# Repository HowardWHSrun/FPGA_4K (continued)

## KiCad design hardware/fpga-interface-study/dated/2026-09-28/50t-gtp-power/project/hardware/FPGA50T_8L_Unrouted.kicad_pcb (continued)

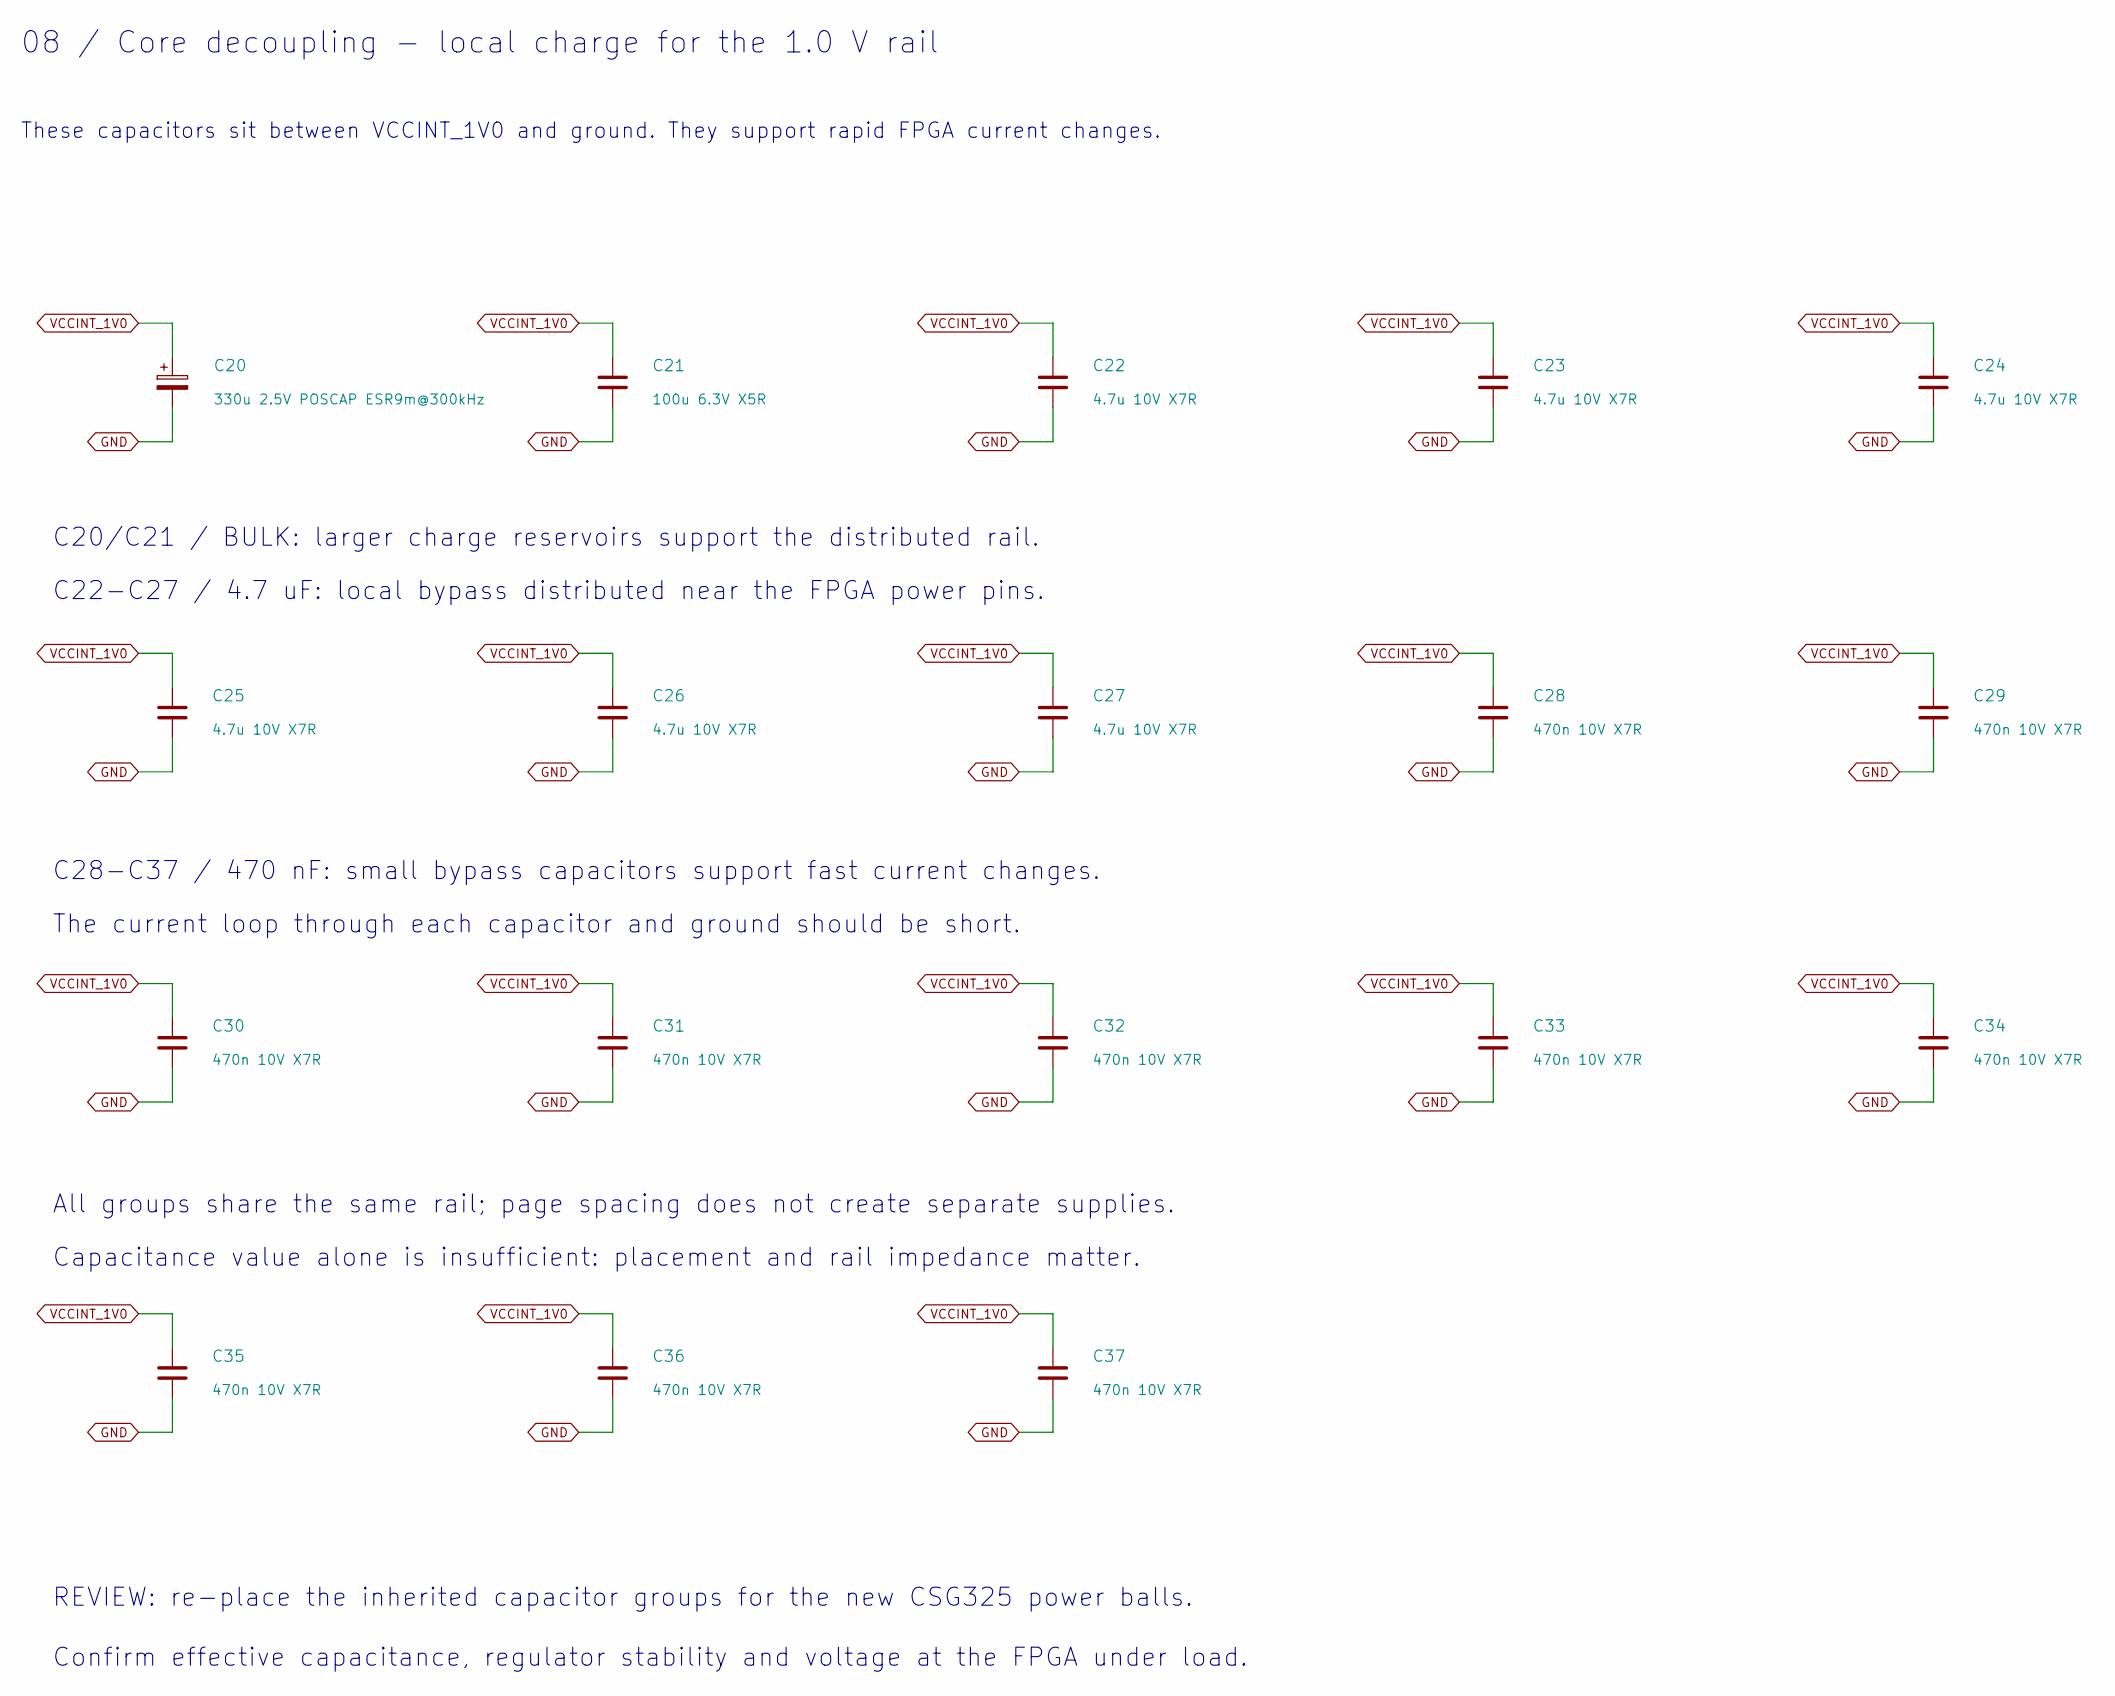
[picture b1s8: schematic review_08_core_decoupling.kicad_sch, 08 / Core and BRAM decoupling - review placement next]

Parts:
C20: 330u 2.5V POSCAP ESR9m@300kHz; Panasonic_POSCAP_B2_Recommended; MPN ETPE330M9GB
C21: 100u 6.3V X5R; Capacitor_SMD__C_1210_3225Metric; MPN GRM32ER60J107ME20L
C22, C23, C24, C25, C26, C27: 4.7u 10V X7R; Capacitor_SMD__C_0805_2012Metric; MPN GRM21BR71A475KA73L
C28, C29, C30, C31, C32, C33, C34, C35, C36, C37: 470n 10V X7R; Murata_GRT15_0402_Recommended; MPN GRT155R71A474KE01D

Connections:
GND: C20.2, C21.2, C22.2, C23.2, C24.2, C25.2, C26.2, C27.2, C28.2, C29.2, C30.2, C31.2, C32.2, C33.2, C34.2, C35.2, C36.2, C37.2; also elsewhere on the board
VCCINT_1V0: C20.1, C21.1, C22.1, C23.1, C24.1, C25.1, C26.1, C27.1, C28.1, C29.1, C30.1, C31.1, C32.1, C33.1, C34.1, C35.1, C36.1, C37.1; also elsewhere on the board

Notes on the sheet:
08 / Core decoupling - local charge for the 1.0 V rail
These capacitors sit between VCCINT_1V0 and ground. They support rapid FPGA current changes.
C20/C21 / BULK: larger charge reservoirs support the distributed rail.
C22-C27 / 4.7 uF: local bypass distributed near the FPGA power pins.
C28-C37 / 470 nF: small bypass capacitors support fast current changes.
The current loop through each capacitor and ground should be short.
All groups share the same rail; page spacing does not create separate supplies.
Capacitance value alone is insufficient: placement and rail impedance matter.
REVIEW: re-place the inherited capacitor groups for the new CSG325 power balls.
Confirm effective capacitance, regulator stability and voltage at the FPGA under load.

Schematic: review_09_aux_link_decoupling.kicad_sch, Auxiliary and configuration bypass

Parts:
C40, C50, C92: 47u 6.3V X7R; Capacitor_SMD__C_1210_3225Metric; MPN GRM32ER70J476ME20L
C41, C42, C51, C52: 4.7u 10V X7R; Capacitor_SMD__C_0805_2012Metric; MPN GRM21BR71A475KA73L
C43, C44, C45, C46, C53, C54, C55, C56: 470n 10V X7R; Murata_GRT15_0402_Recommended; MPN GRT155R71A474KE01D
C90: 100n 16V X7R; Murata_GRT15_0402_Recommended; MPN GRT155R71C104KE01D
C91: 1u 10V X7R; Capacitor_SMD__C_0603_1608Metric; MPN GRM188R71A105KA61D

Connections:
GND: C40.2, C41.2, C42.2, C43.2, C44.2, C45.2, C46.2, C50.2, C51.2, C52.2, C53.2, C54.2, C55.2, C56.2, C90.2, C91.2, C92.2; also elsewhere on the board
VCCAUX_1V8: C40.1, C41.1, C42.1, C43.1, C44.1, C45.1, C46.1, C50.1, C51.1, C52.1, C53.1, C54.1, C55.1, C56.1, C90.1, C91.1, C92.1; also elsewhere on the board

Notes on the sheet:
09 / Auxiliary and configuration bypass
Capacitor groups show placement intent; equal net names are one electrical supply across the board.
1.8 V / AUXILIARY GROUP
CONFIGURATION / SHARED 1.8 V GROUP
C40-C46 + C90/C91 / 1.8 V
These all connect to VCCAUX_1V8.
Large capacitors hold local charge;
smaller values support fast changes.
Review placement near auxiliary/XADC
power pins rather than treating this
as an already isolated analog supply.
C50-C56 + C92 / ALSO 1.8 V
These use the same auxiliary net.
The configuration bank now uses 1.8 V.
The three user I/O banks use 1.5 V.
Redistribute inherited bank capacitors
after reviewing the CSG325 pin map.
NEXT: assign each bypass group to its actual power balls and check the complete power-distribution network.
UNUSED 2.5 V GROUP REMOVED
C57-C63 are no longer fitted.
U4 now feeds GTP1.2 V on sheet13.
New GTP bypass capacitors have
separate analog supply nets.

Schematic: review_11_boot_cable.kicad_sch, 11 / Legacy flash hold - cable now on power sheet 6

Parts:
C100: 100n; Capacitor_SMD__C_0402_1005Metric; MPN GRM155R71C104KA88D
C101: 1u 16V X5R; Capacitor_SMD__C_0402_1005Metric; MPN GRM155R61C105KA12D
R100: 2.4k; Resistor_SMD__R_0402_1005Metric; MPN CRCW04022K40FKED
R101, R102: 4.7k; Resistor_SMD__R_0402_1005Metric; MPN CRCW04024K70FKED
R103, R105: 33; Resistor_SMD__R_0402_1005Metric; MPN CRCW040233R0FKED; not fitted
R104: 0; Resistor_SMD__R_0402_1005Metric; MPN CRCW04020000Z0ED; not fitted
U6: MX25U12835FM2I-10G; Package_SO__SOIC-8_5_3x5_3mm_P1_27mm; MPN MX25U12835FM2I-10G; not fitted

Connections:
FLASH_CS_B: R100.2, U6.1 (~CS)
FLASH_DQ0: R104.2, U6.5 (SI/SIO0)
FLASH_DQ1: R105.2, U6.2 (SO/SIO1)
FLASH_DQ2: R101.2, U6.3 (~WP/SIO2)
FLASH_DQ3: R102.2, U6.7 (~RESET/SIO3)
FLASH_SCLK: R103.2, U6.6 (SCLK)
FPGA_CCLK: R103.1
FPGA_CFG_DQ0: R104.1
FPGA_CFG_DQ1: R105.1
GND: C100.2, C101.2, U6.4 (GND); also elsewhere on the board
VCCAUX_1V8: C100.1, C101.1, R100.1, R101.1, R102.1, U6.8 (VCC); also elsewhere on the board

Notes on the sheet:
11 / Legacy flash and boot-support parts - review hold
DNP means do not populate. Crossed-out parts remain documented but are not a working boot path.
U6 / legacy SPI flash: no connection to U1
FLASH + LOCAL SUPPORT
Flash would store the FPGA configuration.
C100/C101 bypass its supply.
R100-R102 provide inherited pull-up paths.
The complete boot circuit must be reviewed.
R103-R105 / HELD OUT WITH U6
These interface resistors are DNP.
Voltage compatibility and boot mode are open.
Use the JTAG-only proposal for discussion.
J4 and the real power input are on sheet 6.
Do not infer autonomous power-on boot from the presence of a flash symbol.

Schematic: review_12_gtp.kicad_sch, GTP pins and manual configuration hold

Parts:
J6: INIT_B HOLD - shunt before power; Connector_PinHeader_2_54mm__PinHeader_1x02_P2_54mm_Vertical; MPN TBD - 2.54mm 2-pin header and removable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
R123: 100R 1%; Resistor_SMD__R_0402_1005Metric; MPN TBD 100 ohm 1% 0402
U1: XC7A50T-CSG325; Xilinx_CSG325; MPN XC7A50T-CSG325; speed/temperature grade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

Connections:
FPGA_INIT_B: J6.1; also elsewhere on the board
GND: J6.2; also elsewhere on the board
GTP_RREF: R123.1, U1.A6 (MGTRREF_216)
MGTAVCC_1V0: U1.B4 (MGTAVCC), U1.C5 (MGTAVCC), U1.E5 (MGTAVCC), U1.F5 (MGTAVCC); also elsewhere on the board
MGTAVTT_1V2: R123.2, U1.A2 (MGTAVTT), U1.C1 (MGTAVTT), U1.E1 (MGTAVTT), U1.F3 (MGTAVTT), U1.G2 (MGTAVTT); also elsewhere on the board
MGTPRXN0_TBD: U1.E3 (MGTPRXN0_216)
MGTPRXN1_TBD: U1.A3 (MGTPRXN1_216)
MGTPRXN2_TBD: U1.C3 (MGTPRXN2_216)
MGTPRXN3_TBD: U1.G3 (MGTPRXN3_216)
MGTPRXP0_TBD: U1.E4 (MGTPRXP0_216)
MGTPRXP1_TBD: U1.A4 (MGTPRXP1_216)
MGTPRXP2_TBD: U1.C4 (MGTPRXP2_216)
MGTPRXP3_TBD: U1.G4 (MGTPRXP3_216)
MGTPTXN0_TBD: U1.H1 (MGTPTXN0_216)
MGTPTXN1_TBD: U1.F1 (MGTPTXN1_216)
MGTPTXN2_TBD: U1.D1 (MGTPTXN2_216)
MGTPTXN3_TBD: U1.B1 (MGTPTXN3_216)
MGTPTXP0_TBD: U1.H2 (MGTPTXP0_216)
MGTPTXP1_TBD: U1.F2 (MGTPTXP1_216)
MGTPTXP2_TBD: U1.D2 (MGTPTXP2_216)
MGTPTXP3_TBD: U1.B2 (MGTPTXP3_216)
MGTREFCLK0N_TBD: U1.D5 (MGTREFCLK0N_216)
MGTREFCLK0P_TBD: U1.D6 (MGTREFCLK0P_216)
MGTREFCLK1N_TBD: U1.B5 (MGTREFCLK1N_216)
MGTREFCLK1P_TBD: U1.B6 (MGTREFCLK1P_216)

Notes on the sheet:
12 / GTP pins, filtered supplies and manual configuration hold
Four serial channels remain unconnected externally; the new power circuit is on sheet 13.
U1 / SERIAL SIGNAL PINS
TX / RX pairs need a selected external interface.
Dedicated reference-clock source remains open.
U1 / FILTERED ANALOG INPUTS
MGTAVCC_1V0 comes from U7 + FB1.
MGTAVTT_1V2 comes from U4 + FB2.
J6 / INSTALL SHUNT BEFORE POWER
INIT_B low delays configuration during startup.
Measure ALL rails at the FPGA in tolerance/stable.
Remove the shunt; only then begin JTAG configuration.
This is a manual prototype step, not a supervisor.
R123 remains 100 ohm / 1% from MGTRREF to MGTAVTT. GTP I/O and reference-clock design are still open.

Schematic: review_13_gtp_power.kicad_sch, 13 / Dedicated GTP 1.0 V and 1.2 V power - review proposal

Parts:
C11, C124: 22u 25V X5R; Capacitor_SMD__C_1206_3216Metric; MPN MSAST31LBB5226MTNA01
C12, C125: 100n 100V X7R; Capacitor_SMD__C_0603_1608Metric; MPN GRM188R72A104KA35D
C13, C126: 22u 16V X5R; Capacitor_SMD__C_0805_2012Metric; MPN EMK212BBJ226MG-T
C14, C127: 10n 50V X7R; Capacitor_SMD__C_0603_1608Metric; MPN GRM188R71H103KA01D
C128, C131: 4.7u 10V X7R; Capacitor_SMD__C_0805_2012Metric; MPN GRM21BR71A475KA73L
C129, C130, C132, C133: 100n 16V X7R; Murata_GRT15_0402_Recommended; MPN GRT155R71C104KE01D
FB1, FB2: 30R@100MHz / DCR<=10m; TDK_MPZ2012_Recommended; MPN MPZ2012S300AT000
L3, L5: 1uH 5.4A Isat30%; PowerDraft__L_Coilcraft_XFL4020; MPN XFL4020-102MEC
R5: 5.05k 0.1%; Resistor_SMD__R_0603_1608Metric; MPN TBD - exact 0603 0.1% <=25ppm/K orderin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
R6, R125: 6.98k 0.1%; Resistor_SMD__R_0603_1608Metric; MPN TBD - exact 0603 0.1% <=25ppm/K orderin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
R124: 3.10k 0.1%; Resistor_SMD__R_0603_1608Metric; MPN TBD - exact 0603 0.1% <=25ppm/K orderin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
R126, R127: 100k; Resistor_SMD__R_0603_1608Metric; MPN CRCW0603100KFKEA
TP124: TP124; TestPoint__TestPoint_Pad_D1_0mm; MPN PCB test pad
TP125: TP125; TestPoint__TestPoint_Pad_D1_0mm; MPN PCB test pad
TP126: TP126; TestPoint__TestPoint_Pad_D1_0mm; MPN PCB test pad
TP127: TP127; TestPoint__TestPoint_Pad_D1_0mm; MPN PCB test pad
U4, U7: TPS62135RGXR; PowerDraft__Texas_VQFN_RGX0011A_2x3mm; MPN TPS62135RGXR

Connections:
FB_GTP_AVCC: R124.2, R125.1, U7.5 (FB)
FB_GTP_AVTT: R5.2, R6.1, U4.5 (FB)
GND: C11.2, C12.2, C13.2, C14.2, C124.2, C125.2, C126.2, C127.2, C128.2, C129.2, C130.2, C131.2, C132.2, C133.2, R6.2, R125.2, U4.3 (GND), U4.4 (FB2), U4.11 (VSEL), U7.3 (GND), U7.4 (FB2), U7.11 (VSEL); also elsewhere on the board
LINK_12V: C11.1, C12.1, C124.1, C125.1, U4.1 (VIN), U4.10 (MODE), U7.1 (VIN), U7.10 (MODE); also elsewhere on the board
MGTAVCC_1V0: C128.1, C129.1, C130.1, FB1.2, TP124.1; also elsewhere on the board
MGTAVCC_REG_1V011: C126.1, FB1.1, L5.2, R124.1, U7.6 (VOS)
MGTAVTT_1V2: C131.1, C132.1, C133.1, FB2.2, TP125.1; also elsewhere on the board
MGTAVTT_REG_1V206: C13.1, FB2.1, L3.2, R5.1, U4.6 (VOS)
PG_AUX: U7.8 (EN); also elsewhere on the board
PG_GTP_AVCC: R126.2, TP126.1, U4.8 (EN), U7.7 (PG)
PG_GTP_AVTT: R127.2, TP127.1, U4.7 (PG)
SS_GTP_AVCC: C127.1, U7.9 (SS/TR)
SS_GTP_AVTT: C14.1, U4.9 (SS/TR)
SW_GTP_AVCC: L5.1, U7.2 (SW)
SW_GTP_AVTT: L3.1, U4.2 (SW)
VCCAUX_1V8: R126.1, R127.1; also elsewhere on the board

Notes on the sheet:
13 / Dedicated GTP power - core supply remains separate
U7 is new. U4 is reused from the old 2.5 V circuit. These are populated circuit proposals, not measured power rails.
U7 / GTP ANALOG 1.0 V
Regulator setpoint: ~1.0109 V before FB1.
FB1 feeds C128 / C129 / C130 at the FPGA.
U4 / GTP TERMINATION 1.2 V
Regulator setpoint: ~1.2064 V before FB2.
FB2 feeds C131 / C132 / C133 and R123.
WHY TWO DEDICATED RAILS
AMD recommends no sharing
with non-transceiver loads.
U2 still powers core/BRAM.
The common INPUT can be shared.
STARTUP CONNECTIONS
Core PG starts auxiliary U3.
PG_AUX starts U7 and I/O U5.
U7 PG then starts U4.
New PG pull-ups use 1.8 V.
Power-down order is not qualified.
AT EACH GTP SUPPLY GROUP
One 4.7 uF + two 100 nF caps.
Place at assigned supply balls.
FB1/FB2: 10 milliohm max DCR
at the specified test condition.
Verify hot/DC-biased performance.
VOLTAGE / NOISE ACCEPTANCE
MGTAVCC: 0.97-1.03 V.
MGTAVTT: 1.17-1.23 V.
Noise target: below 10 mV p-p
at FPGA pins, 10 kHz-80 MHz.
Filtering is NOT yet measured.
J6 HOLD: SHEET 12
PG is not precision validation.
Measure all rails before JTAG.
XPE load and thermal budget TBD.
Nominal setpoints allow for filter drop. 1 A per rail is a calculation case only; current capacity is not approved.

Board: 8 copper layers, 145 parts (89 on the bottom side), 164 nets, no tracks yet.

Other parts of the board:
C64, C65, C70, C71, C76, C77: 4.7u 10V X7R; Capacitor_SMD__C_0805_2012Metric
C66, C67, C68, C69, C72, C73, C74, C75, C78, C79, C80, C81: 470n 10V X7R; Murata_GRT15_0402_Recommended
C82: 47u 6.3V X7R; Capacitor_SMD__C_1210_3225Metric
H1, H2, H3, H4: M2 PROPOSED / NPTH 2.2; MountingHole_2.2mm_M2

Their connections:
GND: C64.2, C65.2, C66.2, C67.2, C68.2, C69.2, C70.2, C71.2, C72.2, C73.2, C74.2, C75.2, C76.2, C77.2, C78.2, C79.2, C80.2, C81.2, C82.2; also elsewhere on the board
VCC_ASIC_1V5: C64.1, C65.1, C66.1, C67.1, C68.1, C69.1, C70.1, C71.1, C72.1, C73.1, C74.1, C75.1, C76.1, C77.1, C78.1, C79.1, C80.1, C81.1, C82.1; also elsewhere on the board
